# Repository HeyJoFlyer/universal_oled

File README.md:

# Open ESP32 Smart OLED Display Hardware

### Free as in Freedom

This repository provides the complete open-source hardware design for a compact, Wi-Fi-capable smart display using an ESP32 and a 128x64 I2C OLED module. The project includes a manufacturable PCB and a 3D-printable case. An optional capacitive touch sensor can be added to the case.

This project is ideal for developers who want to integrate a small display into smart home interfaces, information kiosks, sensor dashboards, or other embedded projects. Examples include uses with ESPHome for HomeAssistant or weather display.

## Hardware Overview

- ESP32-based design (supports Wi-Fi and Bluetooth)
- 128x64 I2C OLED (SSD1306 or similar)
- Optional touch sensor header (TTP223)
- Compact 3D-printable enclosure
- USB C power
- Designed for easy customization and integration
- Parts sourced from Digikey find list [here](./hardware/components.md)
- Display, touch sensor and USB C port sourced from aliexpress
- PCB ordered from [PCBWay](https://www.pcbway.com)

### PCB Highlights

- Minimal footprint
- Breakout headers for touch input
- Unused GPIO exposed for easy expansion
- Designed using only free software (KiCad and FreeCAD)
- High quality PCB ordered from [PCBWay](https://www.pcbway.com)

## Requirements

- ESP32-WROOM Module (ESP-WROOM-C2)
- 128x64 OLED display with I2C interface
- TTP223 Capacitive Touch sensor module (optional)
- USB C Connector (with 5.1k resistor) for programming and powering the display
- Soldering equipment
- 3D printer for case (optional but recommended)
- PCB

## Usage

This repository provides the physical design only. You are free to write or upload your own firmware using Arduino, PlatformIO, or ESP-IDF. I2C display and touch sensor libraries are widely supported.

For a full list of pin connections and assembly steps, see [hardware/assembly.md](./hardware/assembly.md).

## License

This project is licensed under the MIT License. You are free to use, modify, and distribute it as needed.

## Contributing

Issues and pull requests for improvements to the hardware design or enclosure are welcome.

### Notes
- I have used a cheap USB C breakout to which I added only a single 5.1 k resistor (which is technically is not within USB spec, but it works)
- The antenna of the WROOM module is not blocked by any traces on thee main pcb, however it could possibly interfere with the display. In practice the module works fine and no interference is noticed.
- In the future I will design another open smart display again using an ESP WROOM boards and an SPI LCD Screen.

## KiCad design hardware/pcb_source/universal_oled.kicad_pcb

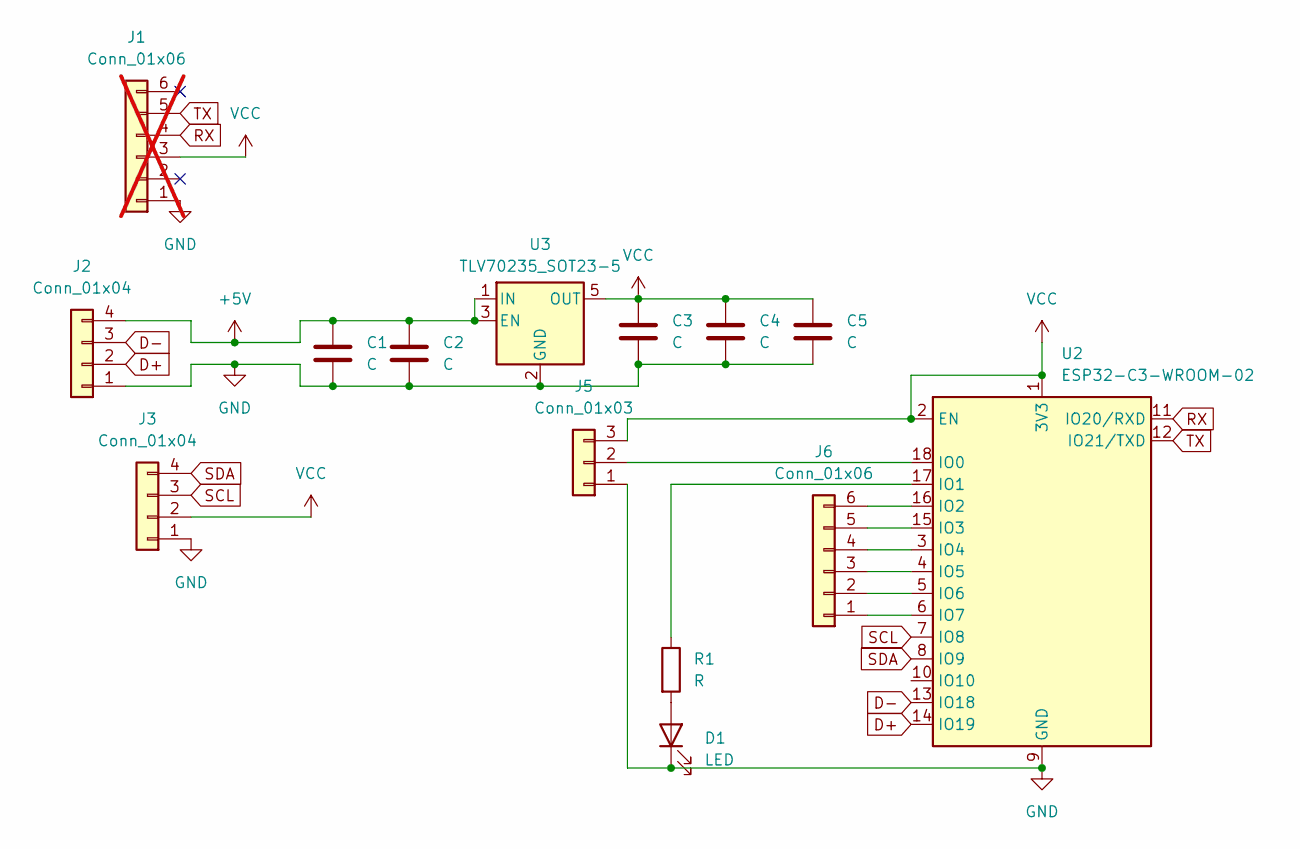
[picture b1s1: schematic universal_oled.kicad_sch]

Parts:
C1, C2, C3, C4: C; C_0603_1608Metric_Pad1.08x0.95mm_HandSolder
C5: C; C_0805_2012Metric_Pad1.18x1.45mm_HandSolder
D1: LED; LED_0805_2012Metric_Pad1.15x1.40mm_HandSolder
J1: Conn_01x06; PinHeader_1x06_P2.54mm_Vertical; not fitted
J2: Conn_01x04; JST_XH_B4B-XH-A_1x04_P2.50mm_Vertical
J3: Conn_01x04; PinHeader_1x04_P2.54mm_Vertical
J5: Conn_01x03; PinHeader_1x03_P2.54mm_Vertical
J6: Conn_01x06; PinHeader_1x06_P2.54mm_Vertical_SMD_Pin1Left
R1: R; R_0603_1608Metric_Pad0.98x0.95mm_HandSolder
U2: ESP32-C3-WROOM-02; ESP-WROOM-02
U3: TLV70235_SOT23-5; SOT-23-5

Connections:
+5V: C1.1, C2.1, J2.4, U3.1 (IN), U3.3 (EN)
D+: J2.2, U2.14 (IO19)
D-: J2.3, U2.13 (IO18)
GND: C1.2, C2.2, C3.2, C4.2, C5.2, D1.1 (K), J1.1, J2.1, J3.1, J5.1, U2.9 (GND), U2.19 (GND), U3.2 (GND)
unnamed: D1.2 (A), R1.2
unnamed: J5.2, U2.18 (IO0)
unnamed: J6.1, U2.6 (IO7)
unnamed: J6.2, U2.5 (IO6)
unnamed: J6.3, U2.4 (IO5)
unnamed: J6.4, U2.3 (IO4)
unnamed: J6.5, U2.15 (IO3)
unnamed: J6.6, U2.16 (IO2)
unnamed: R1.1, U2.17 (IO1)
RX: J1.4, U2.11 (IO20/RXD)
SCL: J3.3, U2.7 (IO8)
SDA: J3.4, U2.8 (IO9)
TX: J1.5, U2.12 (IO21/TXD)
VCC: C3.1, C4.1, C5.1, J1.3, J3.2, J5.3, U2.1 (3V3), U2.2 (EN), U3.5 (OUT)

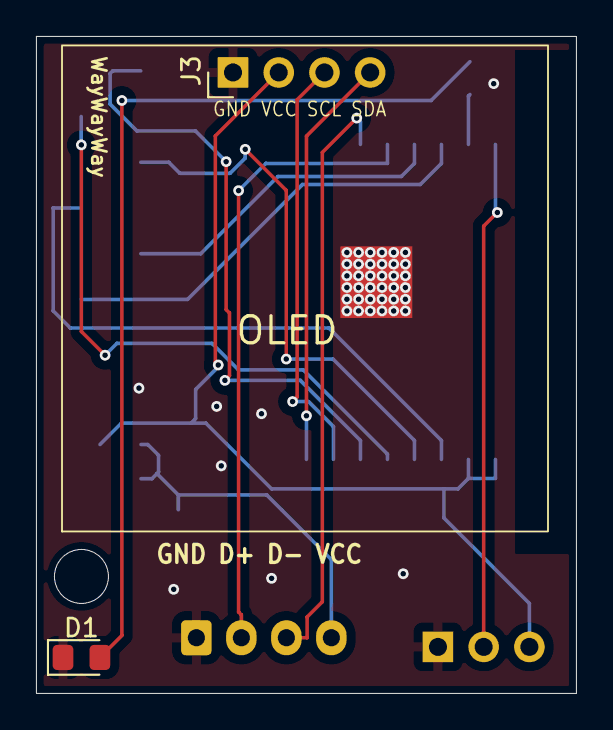
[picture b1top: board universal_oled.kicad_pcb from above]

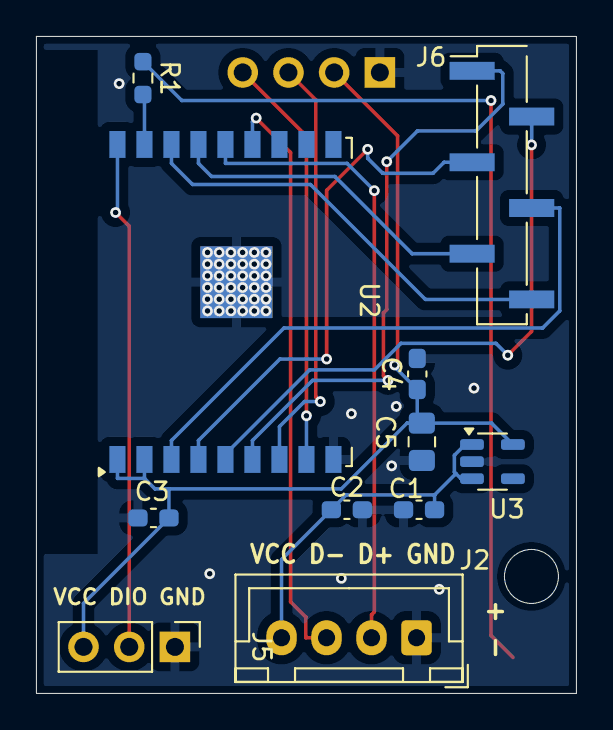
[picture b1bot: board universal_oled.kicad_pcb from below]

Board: 2 copper layers, 30.0 x 36.5 mm, 13 parts (11 on the bottom side), 16 nets.

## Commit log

2025-08-07 Added production files
2025-11-10 New PCB version
